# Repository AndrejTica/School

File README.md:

# Database of HTL-Salzburg related documents and stuff for electronics students.
# This repository is public domain, serving the purpose to benefit students.
# Contribution to the database is welcomed and encouraged.
# Contribution is possible directly with git or by sending an email to: andrejtica@gmail.com

# Klassenlaufwerk tutorial:
# https://www.youtube.com/watch?v=teN9dCBXHyc&feature=youtu.be
# Strasser's EAGLE tutorial channel:
# https://www.youtube.com/channel/UCvcM_29YINRyOCS9GIBd8ow/videos
# Moodle:
# https://elearning2.htl-salzburg.ac.at/Moodle/moodle/

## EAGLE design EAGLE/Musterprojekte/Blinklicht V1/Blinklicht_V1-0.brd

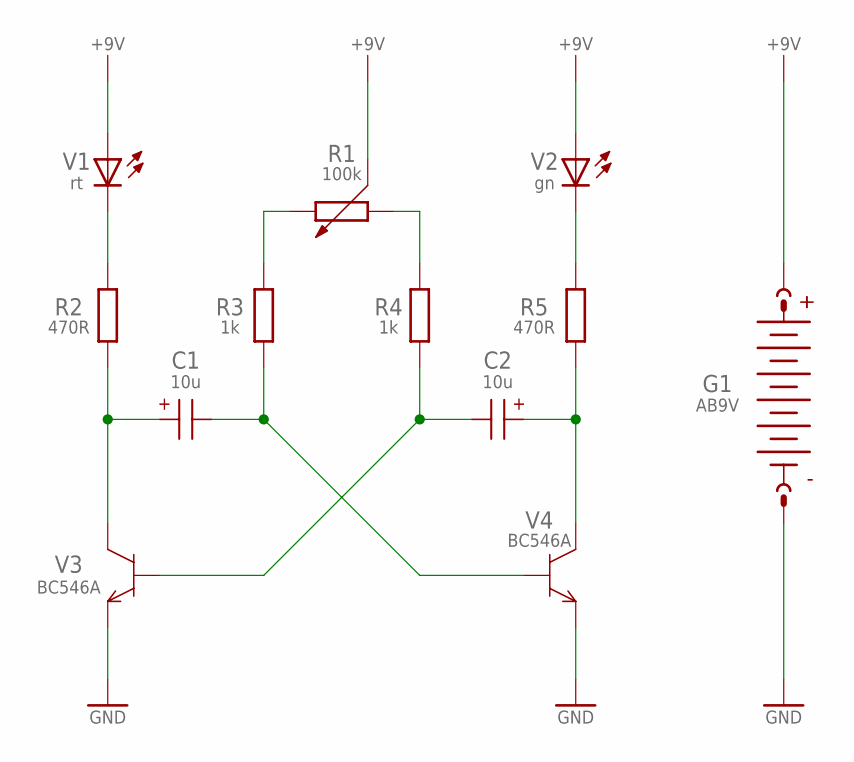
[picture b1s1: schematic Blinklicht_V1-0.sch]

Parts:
C1, C2: 10u; E2-5
G1: AB9V
R1: 100k; PT-10
R2, R5: 470R; 0207/10
R3, R4: 1k; 0207/10
V1: rt; LED3MM
V2: gn; LED3MM
V3, V4: BC546A; TO92-EBC

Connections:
+9V: G1.+, R1.3, V1.A, V2.A
GND: G1.-, V3.E, V4.E
unnamed: R2.2, V1.K (C)
unnamed: C1.+, R2.1, V3.C
unnamed: R1.2, R3.2
unnamed: R1.1, R4.2
unnamed: C1.-, R3.1, V4.B
unnamed: C2.-, R4.1, V3.B
unnamed: C2.+, R5.1, V4.C
unnamed: R5.2, V2.K (C)

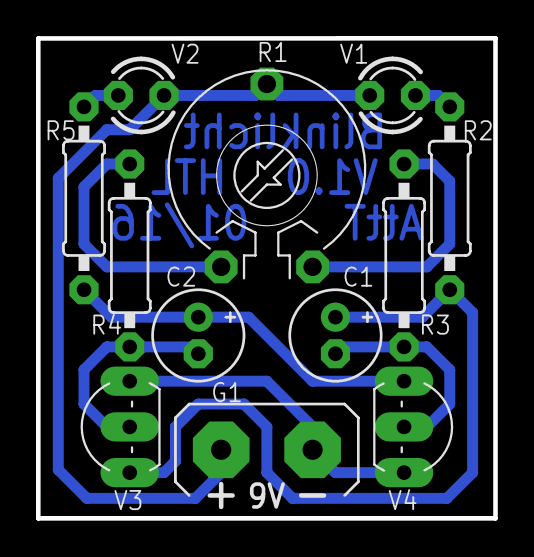
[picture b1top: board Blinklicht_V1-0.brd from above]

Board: 2 copper layers, 25.4 x 26.7 mm, 13 parts (0 on the bottom side), 10 nets.

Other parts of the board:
DRILEGEND: DRILEGEND

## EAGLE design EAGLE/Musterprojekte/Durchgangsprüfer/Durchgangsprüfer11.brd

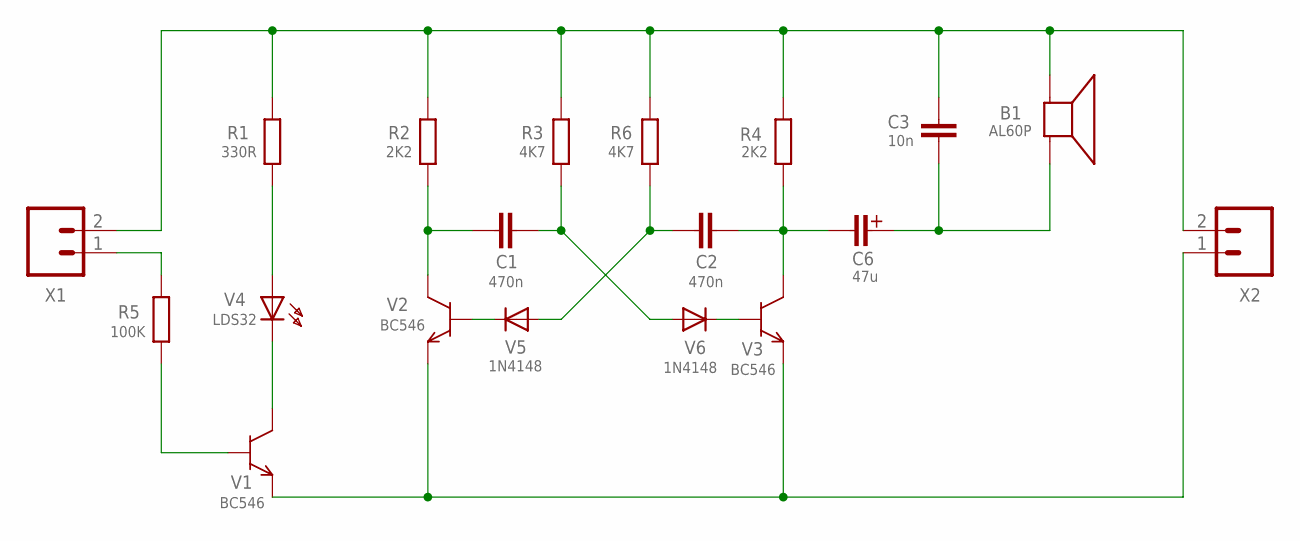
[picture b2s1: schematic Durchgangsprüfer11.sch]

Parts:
B1: AL60P
C1, C2: 470n; C050-024X044
C3: 10n; C050-024X044
C6: 47u; E2,5-6
R1: 330R; 0207/10
R2, R4: 2K2; 0207/10
R3, R6: 4K7; 0207/10
R5: 100K; 0207/10
V1, V2, V3: BC546; TO92IL
V4: LDS32; LED5
V5, V6: 1N4148; D7_5
X1, X2: M02; 02P

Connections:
+12: B1.1, C3.1, R1.2, R2.2, R3.2, R4.2, R6.2, X1.2, X2.2
GND: V1.E, V2.E, V3.E, X2.1
unnamed: C2.1, R6.1, V5.A
unnamed: C1.2, R3.1, V6.A
unnamed: V2.B, V5.C
unnamed: C1.1, R2.1, V2.C
unnamed: V3.B, V6.C
unnamed: C2.2, C6.-, R4.1, V3.C
unnamed: B1.2, C3.2, C6.+
unnamed: R1.1, V4.A
unnamed: V1.C, V4.K (C)
unnamed: R5.2, V1.B
unnamed: R5.1, X1.1

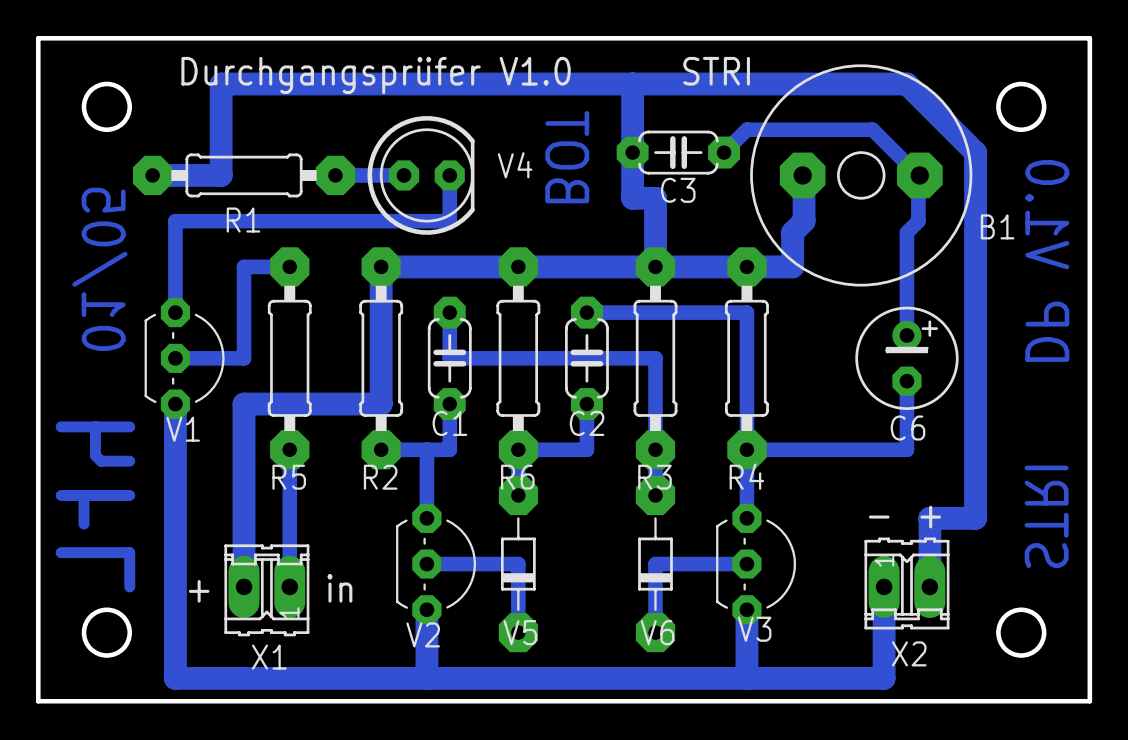
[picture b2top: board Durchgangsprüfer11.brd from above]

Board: 2 copper layers, 58.4 x 36.8 mm, 19 parts (0 on the bottom side), 13 nets.

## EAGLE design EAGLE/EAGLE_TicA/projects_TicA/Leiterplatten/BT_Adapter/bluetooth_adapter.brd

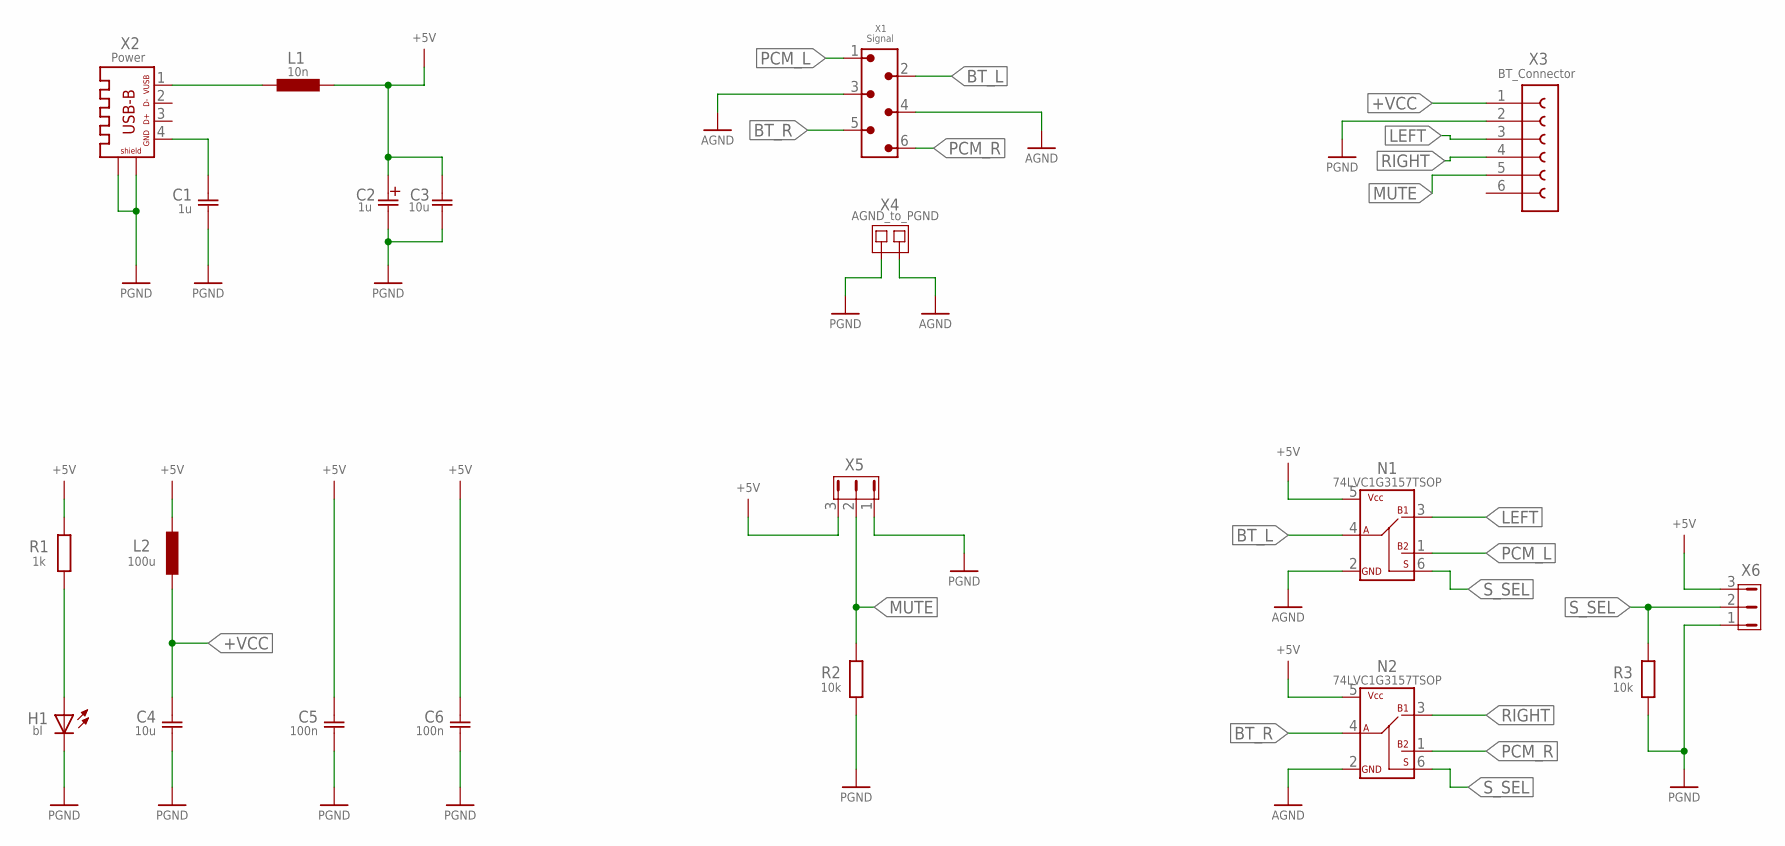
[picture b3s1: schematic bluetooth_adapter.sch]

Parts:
C1: 1u; C3216
C2: 1u; A/3216-18R
C3, C4: 10u; C3216
C5, C6: 100n; C3216
H1: bl; CHIPLED_0805
L1: 10n; L1210
L2: 100u; L0805
N1, N2: 74LVC1G3157TSOP; TSOP6
R1: 1k; R0805
R2, R3: 10k; R0805
X1: Signal; 690357100672
X2: Power; MYLIB_USB-B-LUM
X3: BT_Connector; MYCONNECTORS_FE-1X6_BDIA
X4: AGND_to_PGND; MYLIB_SJ
X5, X6: JP2E; MYLIB_JP2

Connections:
+5V: C2.+, C3.1, C5.1, C6.1, L1.2, L2.2, N1.5 (VCC), N2.5 (VCC), R1.2, X5.3, X6.3
+VCC: C4.1, L2.1, X3.1
AGND: N1.2 (GND), N2.2 (GND), X1.3, X1.4, X4.2
BT_L: N1.4 (A), X1.2
BT_R: N2.4 (A), X1.5
LEFT: N1.3 (B1), X3.3
MUTE: R2.2, X3.5, X5.2
unnamed: H1.A, R1.1
unnamed: C1.1, X2.4
unnamed: L1.1, X2.1
PCM_L: N1.1 (B2), X1.1
PCM_R: N2.1 (B2), X1.6
PGND: C1.2, C2.-, C3.2, C4.2, C5.2, C6.2, H1.C, R2.1, R3.1, X2.SH@1 (SH1), X2.SH@2 (SH2), X3.2, X4.1, X5.1, X6.1
RIGHT: N2.3 (B1), X3.4
S_SEL: N1.6 (S), N2.6 (S), R3.2, X6.2

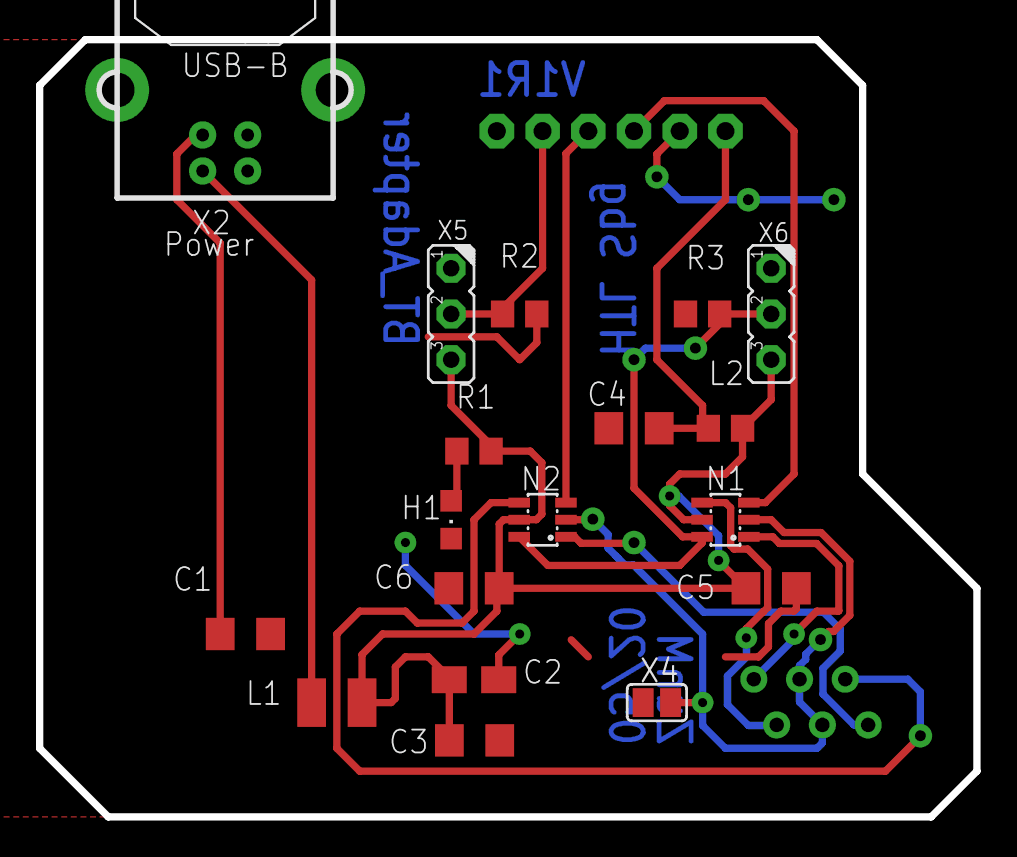
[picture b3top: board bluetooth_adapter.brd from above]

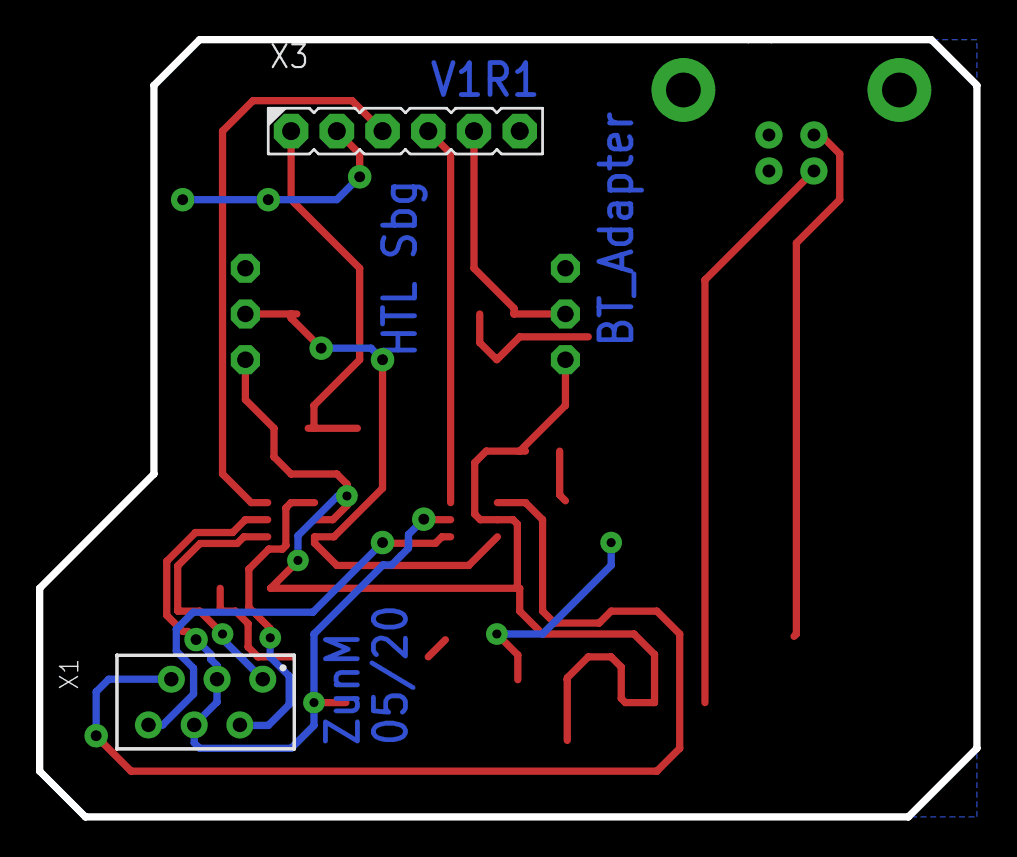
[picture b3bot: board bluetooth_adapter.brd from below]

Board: 2 copper layers, 52.1 x 43.2 mm, 20 parts (2 on the bottom side), 15 nets.

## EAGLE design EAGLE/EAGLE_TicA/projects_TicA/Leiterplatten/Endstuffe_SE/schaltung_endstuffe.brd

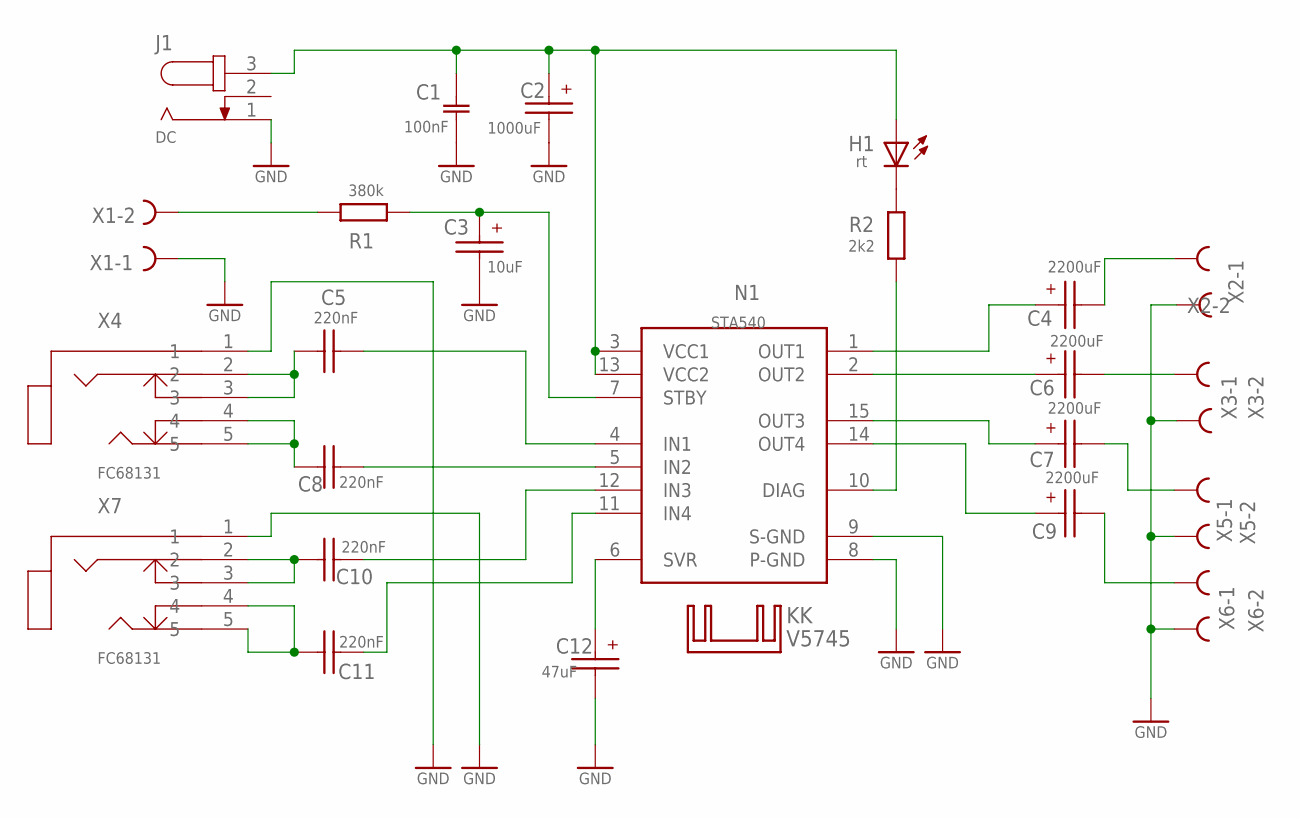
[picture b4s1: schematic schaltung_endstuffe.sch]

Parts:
C1: 100nF; MYLIB_C1206
C2: 1000uF; E7,5-16
C3: 10uF; E3,5-8
C4, C6, C7, C9: 2200uF; E7,5-16
C5, C8, C10, C11: 220nF; C050-025X075
C12: 47uF; E3,5-8
H1: rt; LED5MM
J1: DC; SPC4077
KK: V5745
N1: STA540; MULTIWATT15
R1: 380k; 0204/7
R2: 2k2; 0204/7
X1, X2, X3, X5, X6: AK500/2
X4, X7: FC68131; FC68131-5P

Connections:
GND: C1.+ (2), C2.-, C3.-, C12.-, J1.1, N1.8 (P-GND), N1.9 (S-GND), X1.1, X2.1, X3.2, X4.1, X5.2, X6.2, X7.1
unnamed: C3.+, N1.7 (STBY), R1.2
unnamed: C1.- (1), C2.+, H1.A, J1.3, N1.3 (VCC1), N1.13 (VCC2)
unnamed: C5.1, X4.2, X4.3
unnamed: C10.2, N1.12 (IN3)
unnamed: C8.2, N1.5 (IN2)
unnamed: C10.1, X7.2, X7.3
unnamed: C8.1, X4.4, X4.5
unnamed: C11.2, N1.11 (IN4)
unnamed: C5.2, N1.4 (IN1)
unnamed: C4.+, N1.1 (OUT1)
unnamed: C4.-, X2.2
unnamed: C11.1, X7.4, X7.5
unnamed: C6.+, N1.2 (OUT2)
unnamed: C12.+, N1.6 (SVR)
unnamed: C7.+, N1.15 (OUT3)
unnamed: C9.+, N1.14 (OUT4)
unnamed: C6.-, X3.1
unnamed: C9.-, X6.1
unnamed: C7.-, X5.1
unnamed: R1.1, X1.2
unnamed: H1.K (C), R2.2
unnamed: N1.10 (DIAG), R2.1

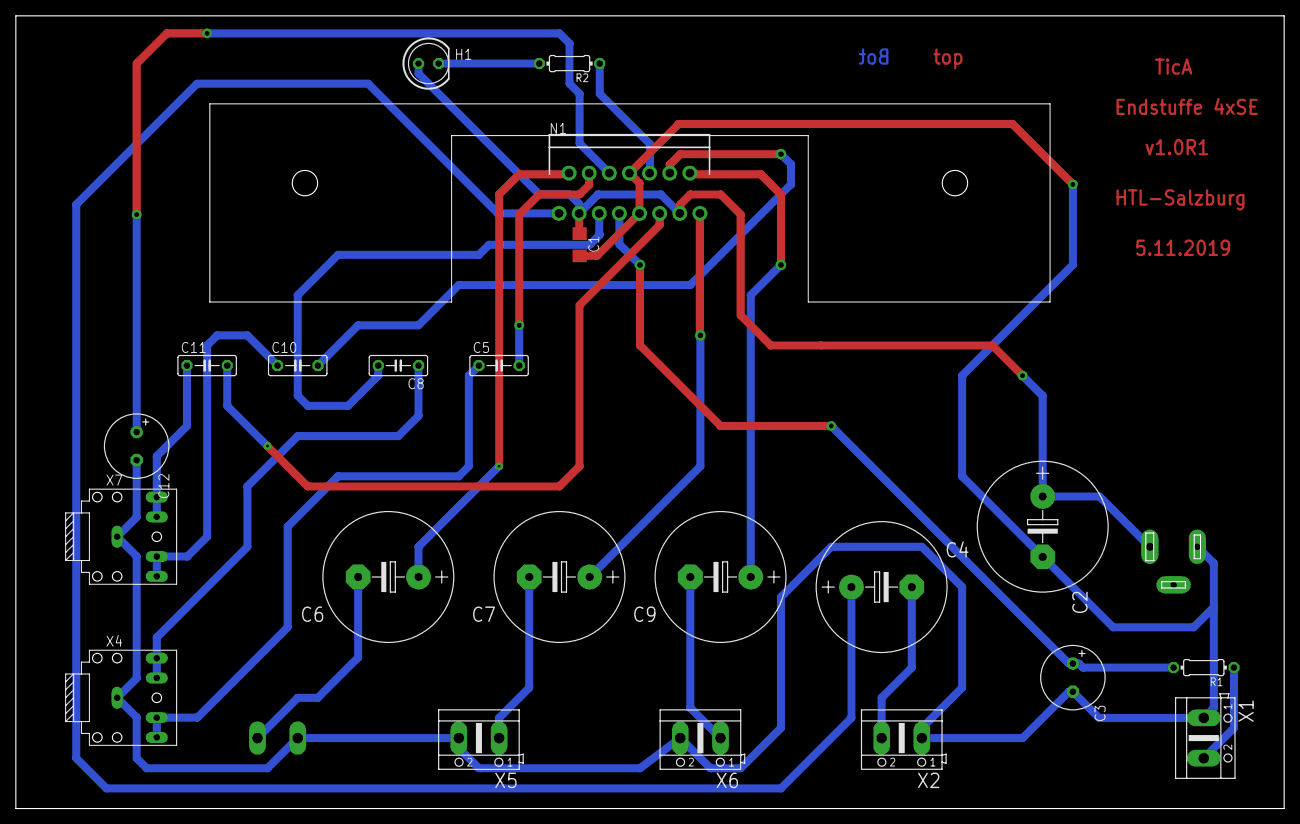
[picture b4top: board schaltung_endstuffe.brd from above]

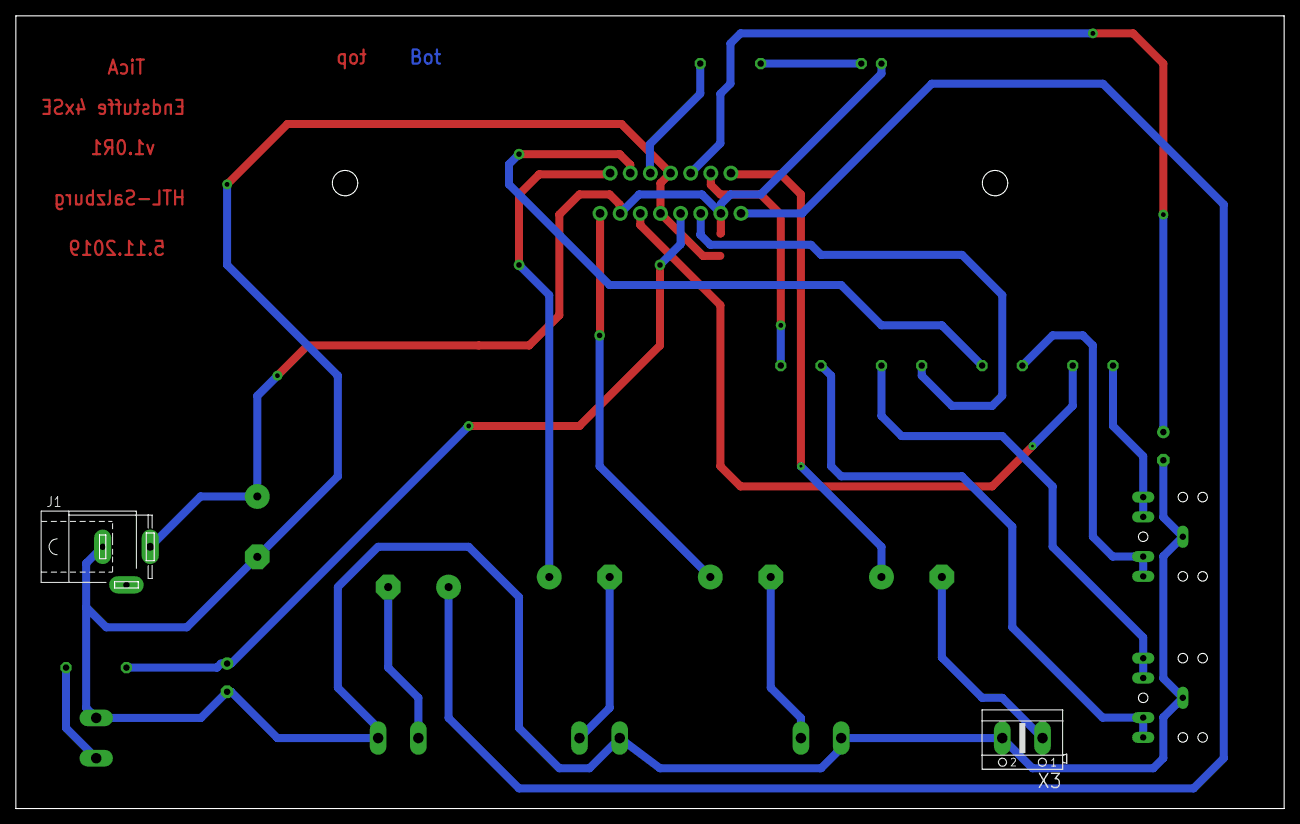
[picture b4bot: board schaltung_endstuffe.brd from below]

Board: 2 copper layers, 160.0 x 100.0 mm, 25 parts (2 on the bottom side), 23 nets.

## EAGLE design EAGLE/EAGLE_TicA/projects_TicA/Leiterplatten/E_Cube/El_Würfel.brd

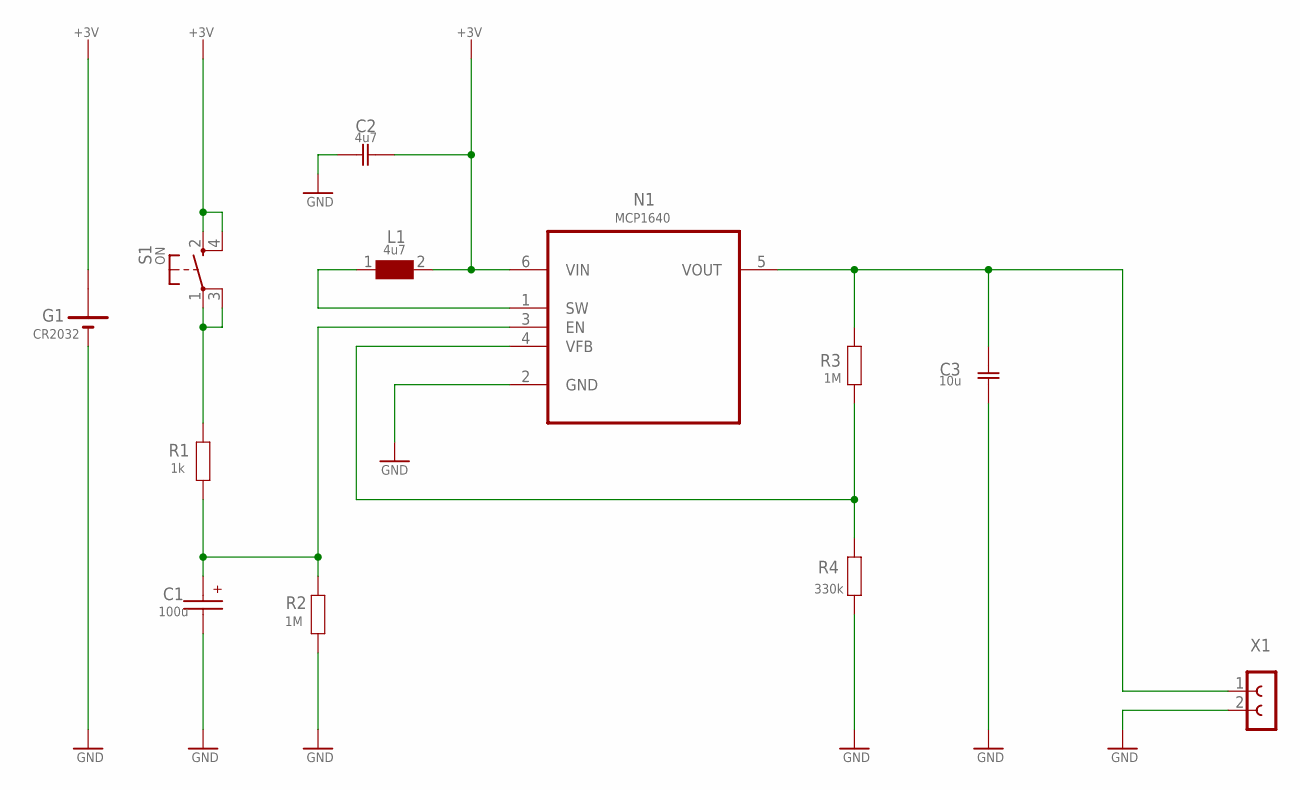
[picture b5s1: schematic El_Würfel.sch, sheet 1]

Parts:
C1: 100u; B/3528-21R
C2: 4u7; MYLIB_C1206
C3: 10u; MYLIB_C1206
G1: CR2032; MYLIB_CR2032
L1: 4u7; WE-PD2_4532
N1: MCP1640; SOT95P270X145-6N
R1: 1k; MYRCL_R1206
R2, R3: 1M; MYRCL_R1206
R4: 330k; MYRCL_R1206
S1: ON; WE_436331045822
X1: BU-LEISTE2; 1X02-SPF-WW

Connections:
+3V: C2.- (1), G1.+@1 (+), L1.2, N1.6 (VIN), S1.2 (S), S1.4 (S1)
GND: C1.-, C2.+ (2), C3.+ (2), G1.-, N1.2 (GND), R2.1, R4.1, X1.2; also elsewhere on the board
unnamed: N1.4 (VFB), R3.1, R4.2
unnamed: L1.1, N1.1 (SW)
unnamed: C3.- (1), N1.5 (VOUT), R3.2, X1.1
unnamed: R1.2, S1.1, S1.3 (P1)
unnamed: C1.+, N1.3 (EN), R1.1, R2.2

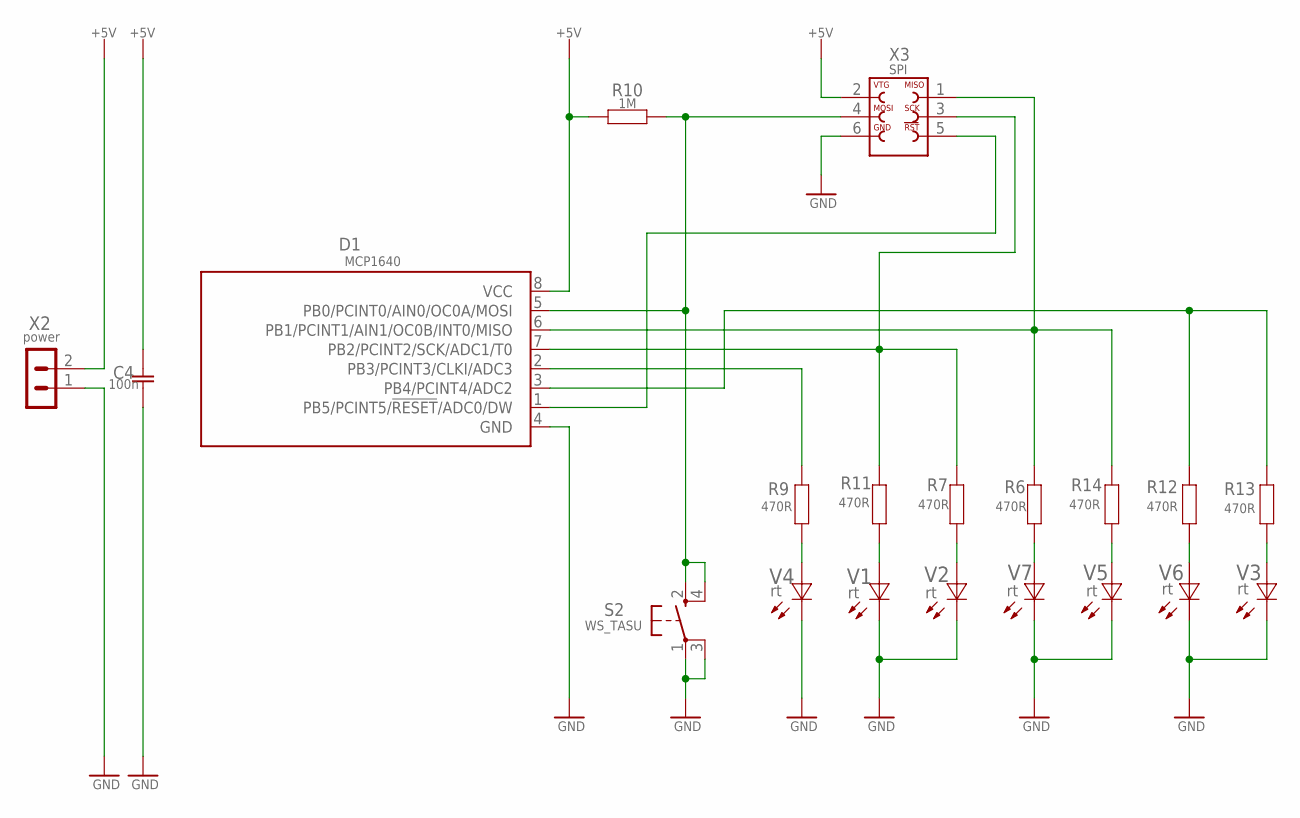
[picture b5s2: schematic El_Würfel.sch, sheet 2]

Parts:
C4: 100n; MYLIB_C1206
D1: MCP1640; 8S2_W
R6, R7, R9, R11, R12, R13, R14: 470R; MYRCL_M1206
R10: 1M; MYRCL_M1206
S2: WS_TASU; WE_436331045822
V1, V2, V3, V4, V5, V6, V7: rt; MYDIODE_CHIPLED_1206
X2: power; 02P
X3: SPI; 690367280676_NEU

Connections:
+5V: C4.- (1), D1.8 (VCC), R10.1, X2.2, X3.2
GND: C4.+ (2), D1.4 (GND), S2.1, S2.3 (P1), V1.C, V2.C, V3.C, V4.C, V5.C, V6.C, V7.C, X2.1, X3.6; also elsewhere on the board
unnamed: D1.1 (PB5/PCINT5/!RESET!/ADC0/DW), X3.5
unnamed: D1.3 (PB4/PCINT4/ADC2), R12.2, R13.2
unnamed: R13.1, V3.A
unnamed: R11.1, V1.A
unnamed: R12.1, V6.A
unnamed: R6.1, V7.A
unnamed: R14.1, V5.A
unnamed: D1.6 (PB1/PCINT1/AIN1/OC0B/INT0/MISO), R6.2, R14.2, X3.1
unnamed: R9.1, V4.A
unnamed: D1.2 (PB3/PCINT3/CLKI/ADC3), R9.2
unnamed: D1.7 (PB2/PCINT2/SCK/ADC1/T0), R7.2, R11.2, X3.3
unnamed: R7.1, V2.A
unnamed: D1.5 (PB0/PCINT0/AIN0/OC0A/MOSI), R10.2, S2.2 (S), S2.4 (S1), X3.4

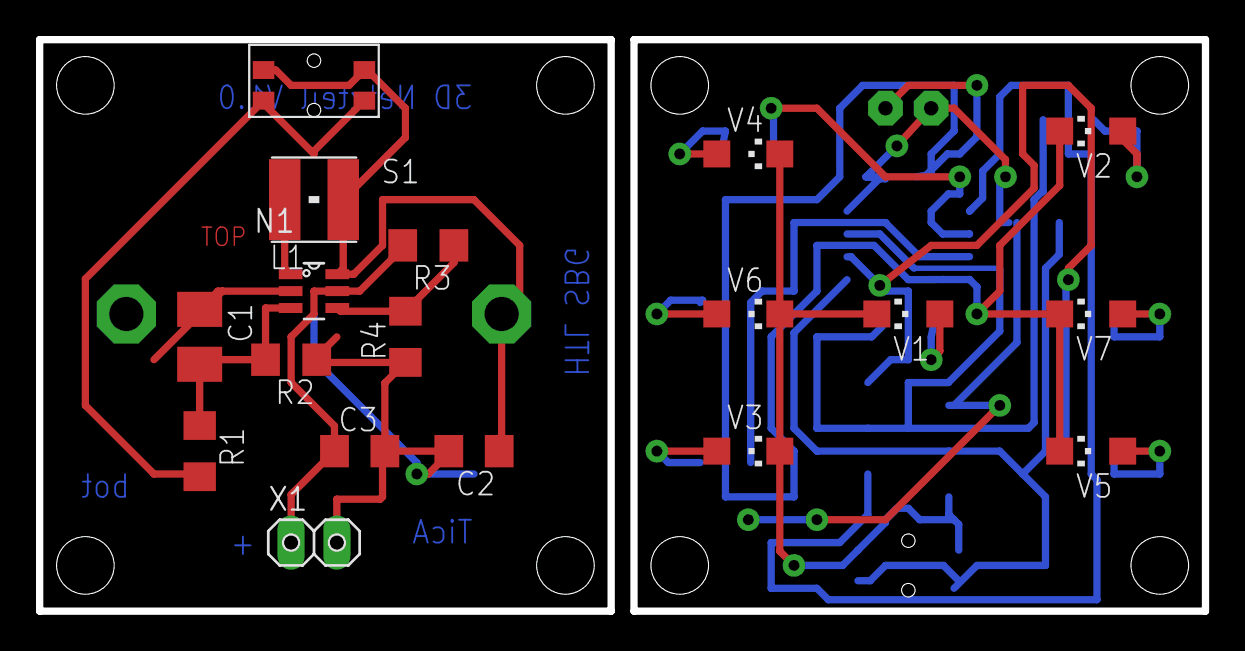
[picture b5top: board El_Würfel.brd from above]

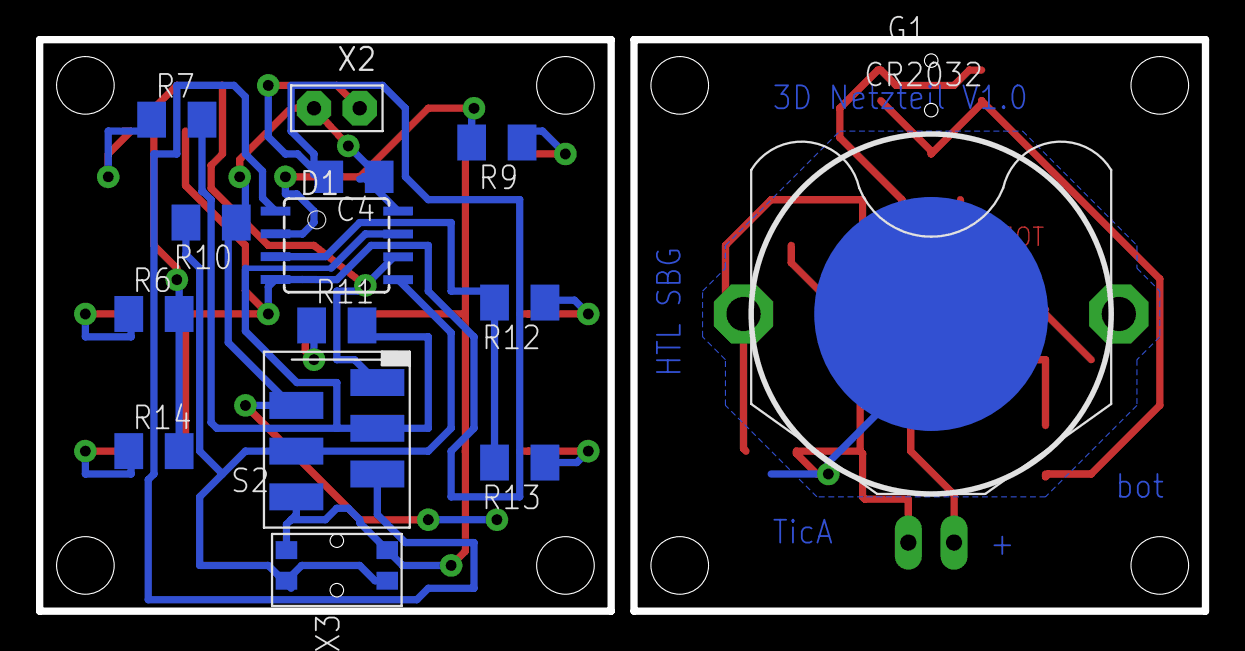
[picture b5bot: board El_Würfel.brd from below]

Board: 2 copper layers, 64.8 x 31.8 mm, 32 parts (14 on the bottom side), 21 nets.

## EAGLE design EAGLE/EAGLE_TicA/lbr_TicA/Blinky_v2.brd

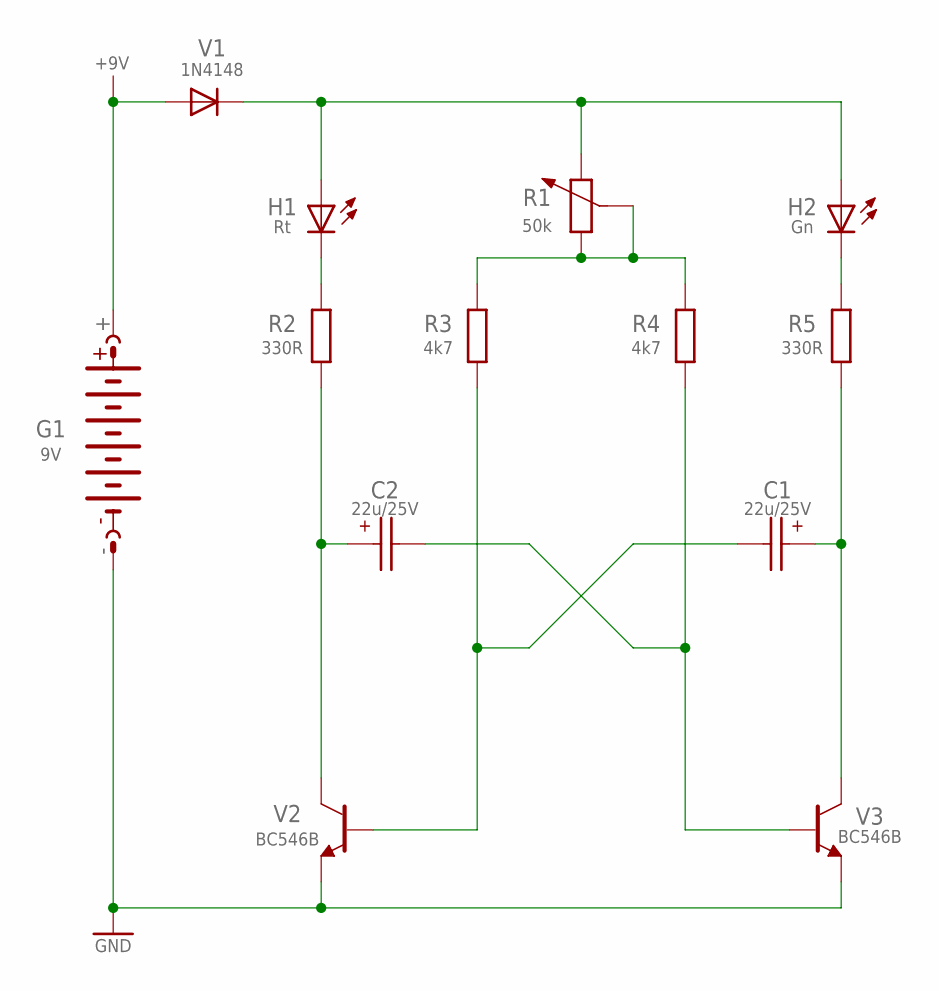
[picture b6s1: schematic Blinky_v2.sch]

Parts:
C1, C2: 22u/25V; E2-5
G1: 9V; AB9V
H1: Rt; LED5MM
H2: Gn; LED5MM
R1: 50k; PT-10
R2, R5: 330R; 0207/10
R3, R4: 4k7; 0207/10
V1: 1N4148; DO35-7
V2, V3: BC546B; TO92-EBC

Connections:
+9V: G1.+, V1.A
GND: G1.-, V2.E, V3.E
unnamed: H1.A, H2.A, R1.2, V1.C
unnamed: R1.1, R1.3, R3.2, R4.2
unnamed: H2.K (C), R5.2
unnamed: H1.K (C), R2.2
unnamed: C2.+, R2.1, V2.C
unnamed: C1.+, R5.1, V3.C
unnamed: C1.-, R3.1, V2.B
unnamed: C2.-, R4.1, V3.B

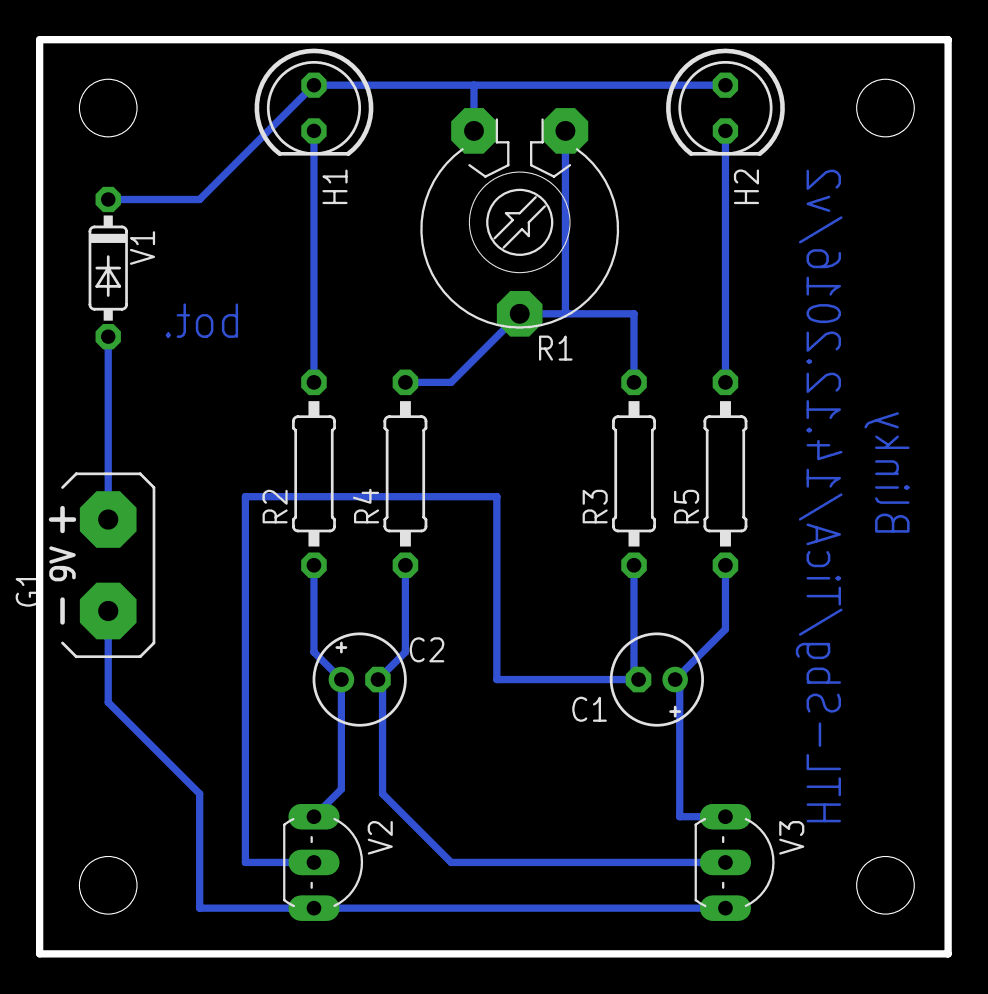
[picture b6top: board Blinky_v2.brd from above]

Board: 2 copper layers, 50.5 x 50.8 mm, 13 parts (0 on the bottom side), 10 nets.

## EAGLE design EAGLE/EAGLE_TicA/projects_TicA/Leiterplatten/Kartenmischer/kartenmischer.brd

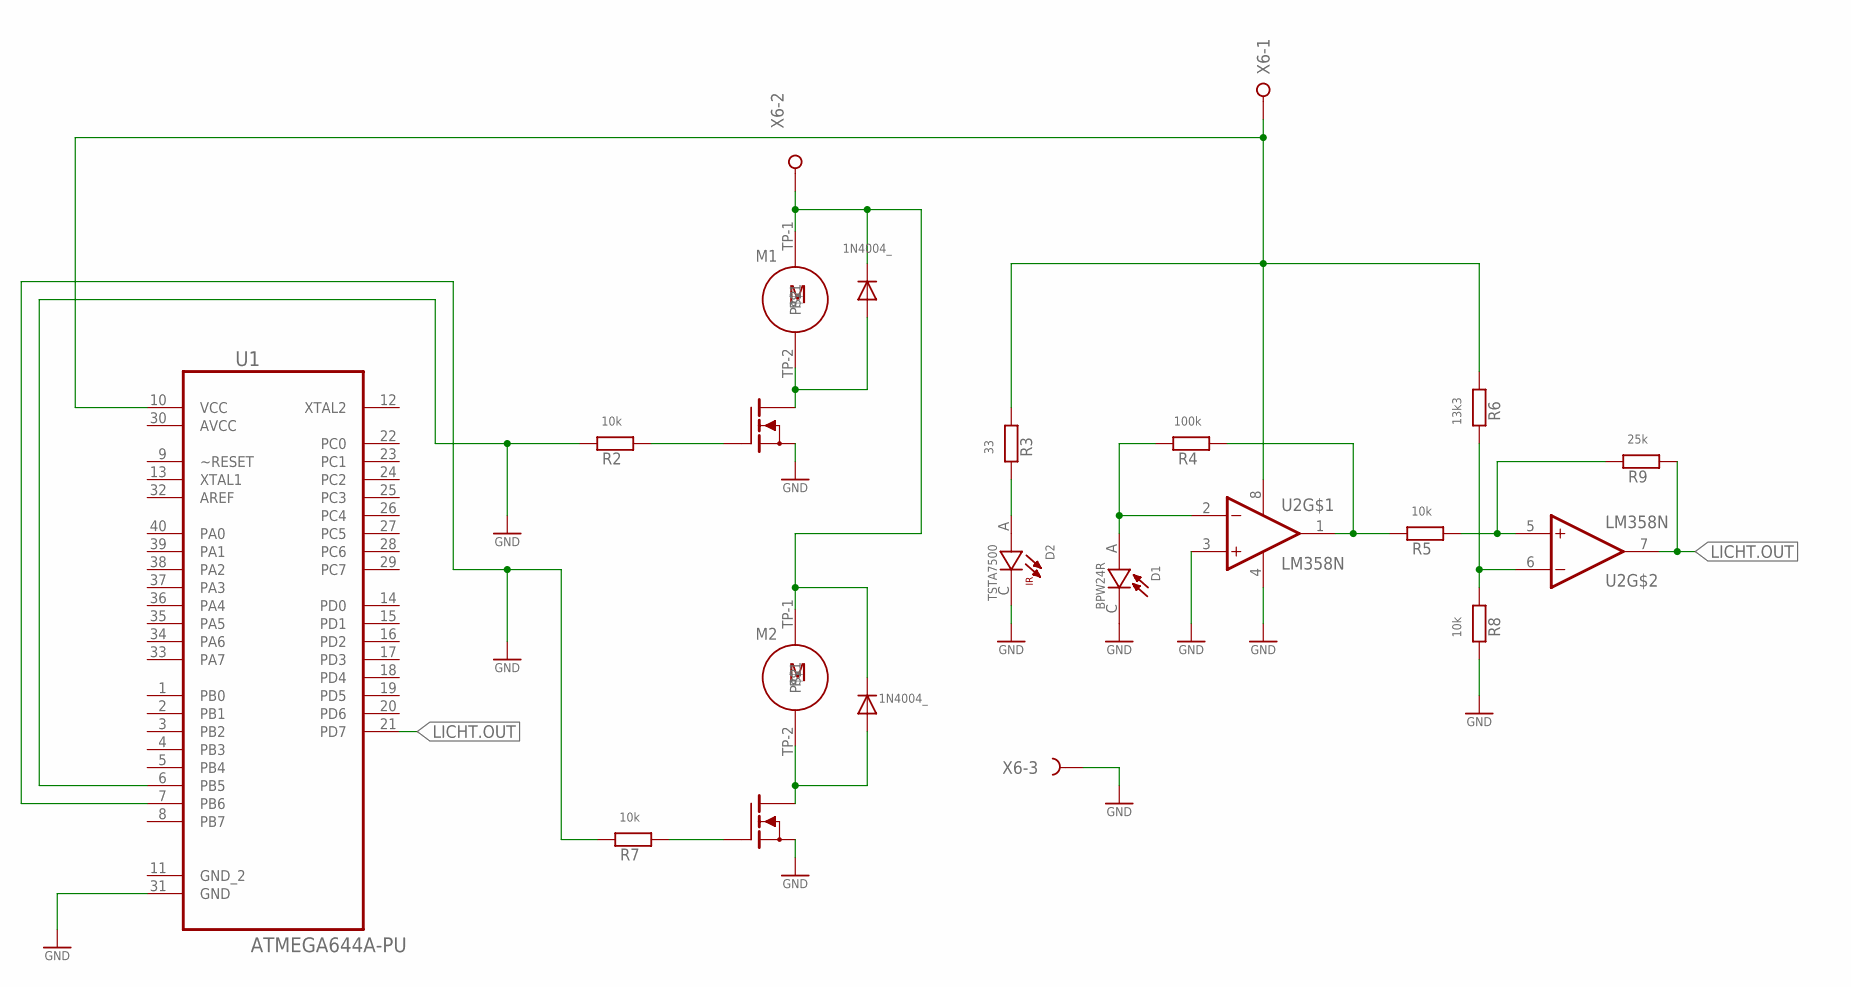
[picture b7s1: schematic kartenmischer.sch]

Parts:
D1: BPW24R; TO127P565H840-2
D2: TSTA7500; TO127P565H745-2
M1, M2: MOTOR; P2-38-17
Q1, Q2: BUZ11; TO220
R2, R5, R7, R8: 10k; 0204/7
R3: 33; 0204/7
R4: 100k; 0204/7
R6: 13k3; 0204/7
R9: 25k; 0204/7
U1: ATMEGA644A-PU; DIP254P1524X483-40
U2: LM358N; DIP762W46P254L960H508Q8
V1, V2: 1N4004_; DO41-10
X6: W237-3E

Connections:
AVCC: U1.30 (AVCC)
GND: D1.C, D2.C, Q1.3 (S), Q2.3 (S), R2.1, R8.1, U1.6 (PB5), U1.31 (GND), U2.3 (1IN+), X6.3
LICHT.OUT: U1.21 (PD7)
unnamed: Q2.1 (G), R7.2
unnamed: R7.1, U1.7 (PB6)
unnamed: Q1.1 (G), R2.2
unnamed: M2.TP-2, Q2.2 (D), V2.A
unnamed: R3.2, R6.2, U1.10 (VCC), U2.8 (VCC), X6.1
unnamed: D2.A, R3.1
unnamed: D1.A, R4.1, U2.2 (1IN-)
unnamed: M1.TP-1, M2.TP-1, V1.C, V2.C, X6.2
unnamed: M1.TP-2, Q1.2 (D), V1.A
unnamed: R4.2, R5.1, U2.1 (1OUT)
unnamed: R5.2, R9.1, U2.5 (2IN+)
unnamed: R9.2, U2.7 (2OUT)
unnamed: R6.1, R8.2, U2.6 (2IN-)
